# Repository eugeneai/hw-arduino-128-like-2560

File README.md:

# Irk-stud-duino (Arduino like) board to arrange studying Real-time systems and Differential equations.

Once I bough sale components in an internet shop.  Now I thought why not use them to in studying Real-time systems and Differential equations.

The components are:

- ICM7555 FET timer module,
- MT30361 Common cathode 7-segment 3-digit LED module,
- M93C86 Microwire EEPROM,
- B57164-K 223-J, 22 кОм, 5%, NTC thermistor (not user now in the PCB),
- 2N3904 N-P-N transistor (not used).

Most of the components wrapped with their pin headers and jumpers, allowing students to study micro controllers with even less soldering.

Printed circuit design for Arduino Mega v3.0.3-like board based on ATMega-128,-64, which has TQFP-64 package (not TQFP-100). These chips are cheap now when bought at ALIExpress.

__ATTENTION! This PCB Design is not complete, e.g., it is not pin-compatible with Arduino Mega.__

## TODO:

- Move big components on the top of PCB (swap sides).
- Add an N-P-N transistor in key mode with some components to connect output of 7555, *e.g.*, with a relay.
- Move silk text to a visible place.
- Use SMD Capacitors around 5V rectifier.
- Write a handbook.

PCB made with/by KiCAD and FreeRouting.

## Current scheme

## Current PCB layout

License - MIT.

Regards,
Evgeny Cherkashin, Ph.D.
Irkutsk

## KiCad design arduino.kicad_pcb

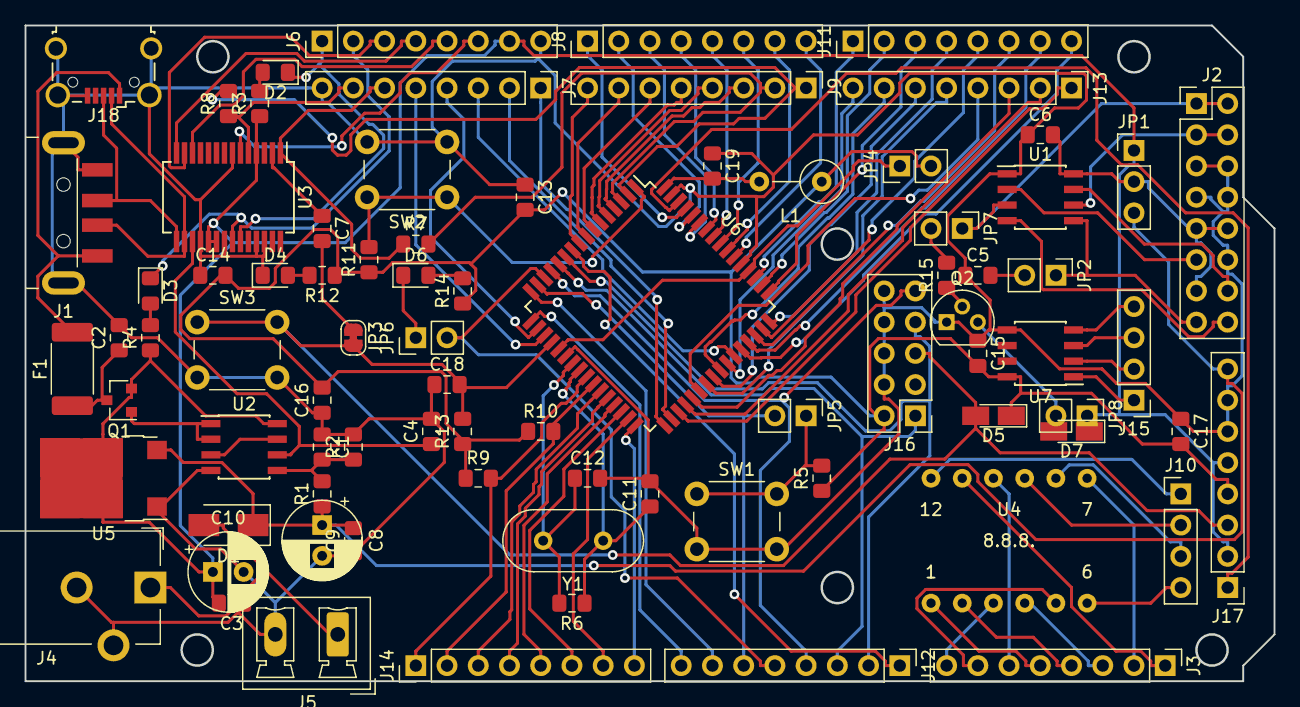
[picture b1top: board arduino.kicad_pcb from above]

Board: 2 copper layers, 101.5 x 53.3 mm, 82 parts (0 on the bottom side), 116 nets.

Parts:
C1, C2, C4, C9: 100n; C_0805_2012Metric_Pad1.15x1.40mm_HandSolder
C3, C7: 0.1u; C_0805_2012Metric_Pad1.15x1.40mm_HandSolder
C5: C 10n; C_0805_2012Metric_Pad1.15x1.40mm_HandSolder
C6, C13, C14, C15, C16, C17: C 100n; C_0805_2012Metric_Pad1.15x1.40mm_HandSolder
C8, C10: 47u; CP_Radial_D6.3mm_P2.50mm
C11, C12: 22p; C_0805_2012Metric_Pad1.15x1.40mm_HandSolder
C18: 1u; C_0805_2012Metric_Pad1.15x1.40mm_HandSolder
C19: 0.1m; C_0805_2012Metric_Pad1.15x1.40mm_HandSolder
D1: M7; D_SMA
D2, D3, D4, D6: LED; LED_0805_2012Metric_Pad1.15x1.40mm_HandSolder
D5, D7: 4148; D_MicroMELF_Hadsoldering
F1: 0.5RST; Fuse_2512_6332Metric_Pad1.52x3.35mm_HandSolder
J1: USB_A; USB_A_CNCTech_1001-011-01101_Horizontal
J2: NE7555; PinHeader_2x08_P2.54mm_Vertical
J3: 7SEG; PinHeader_1x08_P2.54mm_Vertical
J4: DCJ0202; BarrelJack_CUI_PJ-102AH_Horizontal
J5: PWR; PhoenixContact_MCV_1,5_2-G-5.08_1x02_P5.08mm_Vertical
J6: UART; PinHeader_1x08_P2.54mm_Vertical
J7: PG; PinHeader_1x08_P2.54mm_Vertical
J8: PF; PinHeader_1x08_P2.54mm_Vertical
J9: PE; PinHeader_1x08_P2.54mm_Vertical
J10: 7SEL; PinHeader_1x04_P2.54mm_Vertical
J11: PA; PinHeader_1x08_P2.54mm_Vertical
J12: PB; PinHeader_1x08_P2.54mm_Vertical
J13: PC; PinHeader_1x08_P2.54mm_Vertical
J14: PD; PinHeader_1x08_P2.54mm_Vertical
J15: MICROWIRE; PinHeader_1x04_P2.54mm_Vertical
J16: ISP; PinHeader_2x05_P2.54mm_Vertical
J17: POWER; PinHeader_1x08_P2.54mm_Vertical
J18: USB_B_Micro; USB_Micro-B_Wuerth_629105150521_CircularHoles
JP1: 5v/vin; PinHeader_1x03_P2.54mm_Vertical
JP2: CTLR; PinHeader_1x02_P2.54mm_Vertical
JP3: AVR; SolderJumper-2_P1.3mm_Bridged_RoundedPad1.0x1.5mm
JP4, JP6: Jumper; PinHeader_1x02_P2.54mm_Vertical
JP5: JOP; PinHeader_1x02_P2.54mm_Vertical
JP7: NPN; PinHeader_1x02_P2.54mm_Vertical
JP8: RELAY; PinHeader_1x02_P2.54mm_Vertical
L1: L; L_Axial_L7.0mm_D3.3mm_P5.08mm_Vertical_Fastron_MICC
Q1: FDN340P; SOT-23
Q2: 2N3903; TO-92
R1, R2, R5, R9, R10, R11, R13: 10k; R_0805_2012Metric_Pad1.15x1.40mm_HandSolder
R3, R4, R12, R14, R15: 1k; R_0805_2012Metric_Pad1.15x1.40mm_HandSolder
R6: 1M; R_0805_2012Metric_Pad1.15x1.40mm_HandSolder
R7, R8: R 1k; R_0805_2012Metric_Pad1.15x1.40mm_HandSolder
SW1: OP; SW_PUSH_6mm
SW2: PRG; SW_PUSH_6mm
SW3: RST; SW_PUSH_6mm
U1: ICM7555; SOIC-8_3.9x4.9mm_P1.27mm
U2: LM358; SOIC-8_3.9x4.9mm_P1.27mm
U3: FT232RL; SSOP-28_5.3x10.2mm_P0.65mm
U4: MT30361; 7Segment-3-12.7x10.16
U5: MC33269D-5.0; ATPAK-2
U6: ATmega128-16AU; TQFP-64_14x14mm_P0.8mm
U7: M93C86-WMN6TP; SOIC-8_3.9x4.9mm_P1.27mm
Y1: Crystal; Crystal_HC49-4H_Vertical

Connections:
3v3: C4.1, U2.6, U3.17
+5V: C3.2, C10.1, D7.1, J6.7, J17.2, J17.5, JP1.1, JP8.1, Q1.2, R3.1, R4.1, U2.8, U3.4, U3.19, U3.20, U5.2
EECS: J15.1, U7.1
NECTRLV: J2.15, JP2.1, U1.5
NEDIS: J2.14, U1.7
NEGND: C1.1, C2.2, C3.1, C4.2, C5.1, C6.1, C8.2, C9.1, C10.2, C11.2, C12.2, C13.1, C14.1, C15.1, C16.1, C17.1, C18.1, C19.1, D4.1, J1.4, J1.5, J2.5, J2.6, J2.7, J2.8, J2.12, J4.2, J4.3, J5.2, J6.8, J7.8, J16.4, J16.6, J16.8, J16.10, J17.6, J17.7, J18.5, J18.6, Q2.1, R2.2, SW1.2, SW2.2, SW3.2, U1.1, U2.4, U3.7, U3.18, U3.21, U3.25, U3.26, U5.1, U6.22, U6.53, U6.63, U7.5
NENRST: J2.16, U1.4
NENTRIG: J2.11, U1.2
NEOUT: J2.1, J2.2, JP7.1, U1.3
NETHR: J2.3, J2.4, U1.6
NEVCC: C6.2, J2.9, J2.10, J2.13, JP1.2, U1.8
unnamed: C5.2, JP2.2
unnamed: C7.1, U3.2
unnamed: C7.2, JP3.1
unnamed: D2.2, R3.2
unnamed: D3.2, R4.2
unnamed: D4.2, R12.2
unnamed: D6.1, JP6.1
unnamed: D6.2, R14.2
unnamed: D7.2, JP8.2, Q2.3
unnamed: J1.2, J18.2, U3.16
unnamed: J1.3, J18.3, U3.15
unnamed: J3.1, U4.11
unnamed: J3.2, U4.7
unnamed: J3.3, U4.4
unnamed: J3.4, U4.2
unnamed: J3.5, U4.1
unnamed: J3.6, U4.10
unnamed: J3.7, U4.5
unnamed: J3.8, U4.3
unnamed: J8.1, U6.61
unnamed: J8.2, U6.60
unnamed: J8.3, U6.59
unnamed: J8.4, U6.58
unnamed: J8.5, U6.57
unnamed: J8.6, U6.56
unnamed: J8.7, U6.55
unnamed: J8.8, U6.54
unnamed: J9.3, U6.4
unnamed: J9.4, U6.5
unnamed: J9.5, U6.6
unnamed: J9.6, U6.7
unnamed: J9.7, U6.8
unnamed: J9.8, U6.9
unnamed: J10.1, U4.12
unnamed: J10.2, U4.9
unnamed: J10.3, U4.8
unnamed: J10.4, U4.6
unnamed: J11.1, U6.51
unnamed: J11.2, U6.50
unnamed: J11.3, U6.49
unnamed: J11.4, U6.48
unnamed: J11.5, U6.47
unnamed: J11.6, U6.46
unnamed: J11.7, U6.45
unnamed: J11.8, U6.44
unnamed: J12.1, U6.10
unnamed: J12.7, U6.16
unnamed: J12.8, U6.17
unnamed: J13.1, U6.35
unnamed: J13.2, U6.36
unnamed: J13.3, U6.37
unnamed: J13.4, U6.38
unnamed: J13.5, U6.39
unnamed: J13.6, U6.40
unnamed: J13.7, U6.41
unnamed: J13.8, U6.42
unnamed: J14.3, U6.27
unnamed: J14.4, U6.28
unnamed: J14.5, U6.29
unnamed: J14.6, U6.30
unnamed: J14.7, U6.31
unnamed: J14.8, U6.32
unnamed: J15.2, U7.2
unnamed: J15.3, U7.3
unnamed: J15.4, U7.4
unnamed: JP4.1, U6.21, U6.52
unnamed: JP5.1, R5.2, SW1.1
unnamed: JP7.2, R15.2
unnamed: Q2.2, R15.1
unnamed: U2.3, U2.7
VCC: C13.2, C14.2, C15.2, C16.2, C17.2, D5.1, J16.2, J17.4, JP4.2, L1.1, R5.1, R9.1, R10.1, R11.1, R12.1, R13.1, R14.1, U7.8
ale: J7.3, U6.43
aref: J17.1, U6.62
avcc: C19.2, L1.2, U6.64
cbus0: D2.1, J6.1, U3.23
cbus1: D3.1, J6.2, U3.22
cbus2: J6.3, U3.13
cbus3: J6.4, U3.14
cbus4: J6.5, U3.12
cmp: C1.2, R1.2, R2.1, U2.5
gate_cmd: Q1.1, U2.1, U2.2
m8rxd: J7.7, R8.1, U3.5
m8txd: J7.6, R7.1, U3.1
miso: J12.4, J16.9, U6.13
mosi: J12.3, J16.1, U6.12
npen: R11.2, SW2.1, U6.1
nrd: J7.2, U6.34
nwr: J7.1, U6.33
pb4: J12.5, JP6.2, U6.14
pb5: J12.6, JP5.2, U6.15
pwrin: D1.2, J4.1, J5.1
reset: C18.2, D5.2, J16.5, J17.3, JP3.2, R13.2, SW3.1, U6.20
ring: J6.6, U3.6
rxd: J9.1, R8.2, U6.2
sck: J12.2, J16.7, U6.11
scl: J14.1, R9.2, U6.25
sda: J14.2, R10.2, U6.26
tosc1: J7.5, U6.19
tosc2: J7.4, U6.18
txd: J9.2, R7.2, U6.3
usbvbus: F1.2, J1.1, J18.1
usbvcc: C2.1, F1.1, Q1.3
vin: C8.1, C9.2, D1.1, J17.8, JP1.3, R1.1, U5.3
xtal1: C11.1, R6.1, U6.24, Y1.1
xtal2: C12.1, R6.2, U6.23, Y1.2

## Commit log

2019-02-02 Initial import
2019-02-03 Made the handcraft design
2019-02-03 Added Readme.
2019-02-03 Added views.
2019-02-04 After a night of Freerouting optimization.
2019-02-04 Added SVG view of PCB.
2019-02-04 Ignore autosaves.
2019-02-04 Added scheme as a view.
2019-02-04 Added a line to TODO.
2019-02-04 Added some nice history.
2019-02-04 Renewal of story stages.
2019-02-04 Wrong name of a component.
2019-02-04 TODO bug.
2019-02-04 Another todo bug
2019-02-04 Added NPN transistor
2019-02-04 Routed
2019-02-05 Plotted new scheme and PCB
